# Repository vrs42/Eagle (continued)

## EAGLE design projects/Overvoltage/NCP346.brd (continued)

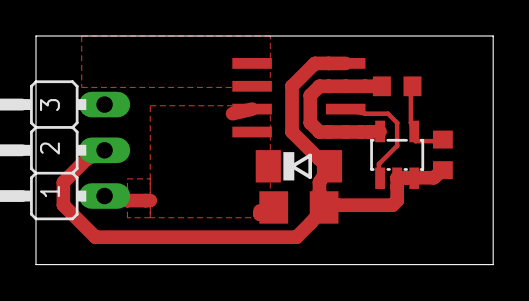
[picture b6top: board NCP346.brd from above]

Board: 2 copper layers, 25.4 x 12.7 mm, 7 parts (0 on the bottom side), 6 nets.
